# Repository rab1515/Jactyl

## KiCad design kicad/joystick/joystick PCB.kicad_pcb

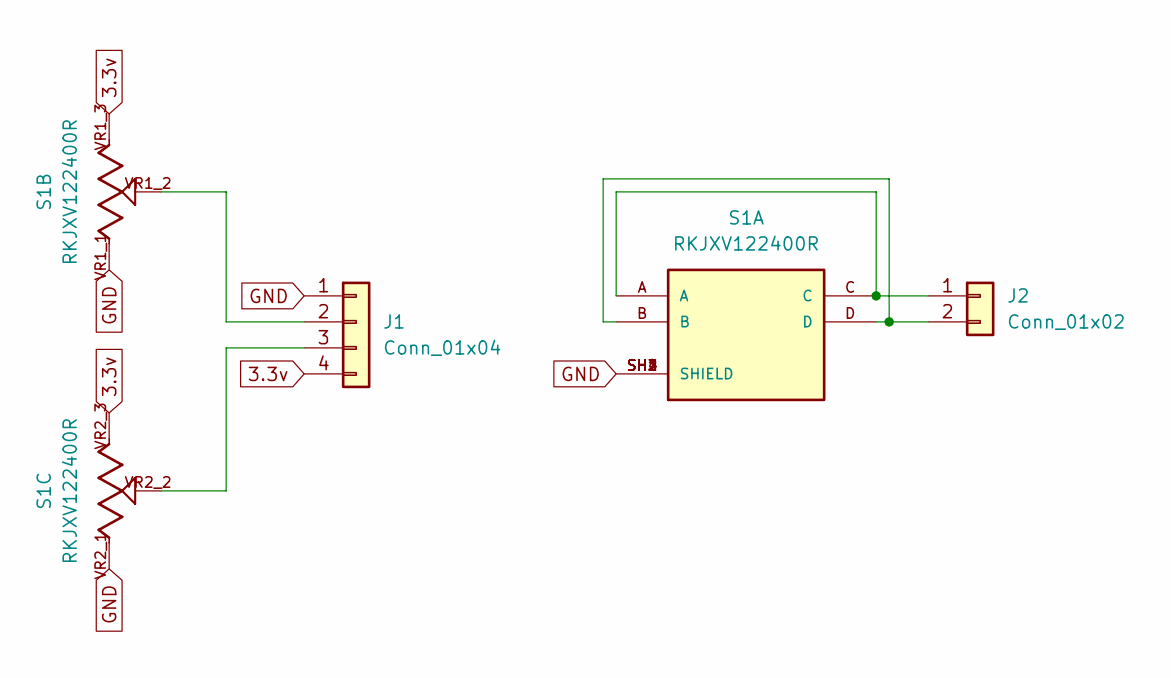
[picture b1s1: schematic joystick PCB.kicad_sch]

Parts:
J1: Conn_01x04; JST_PH_B4B-PH-K_1x04_P2.00mm_Vertical
J2: Conn_01x02; JST_PH_B2B-PH-K_1x02_P2.00mm_Vertical
S1: RKJXV122400R; SW_RKJXV122400R; PARTREV N/A

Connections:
3.3v: J1.4, S1.VR1_3, S1.VR2_3
GND: J1.1, S1.SH1 (SHIELD), S1.SH2 (SHIELD), S1.SH3 (SHIELD), S1.SH4 (SHIELD), S1.VR1_1, S1.VR2_1
unnamed: J1.2, S1.VR1_2
unnamed: J1.3, S1.VR2_2
unnamed: J2.1, S1.A, S1.C
unnamed: J2.2, S1.B, S1.D

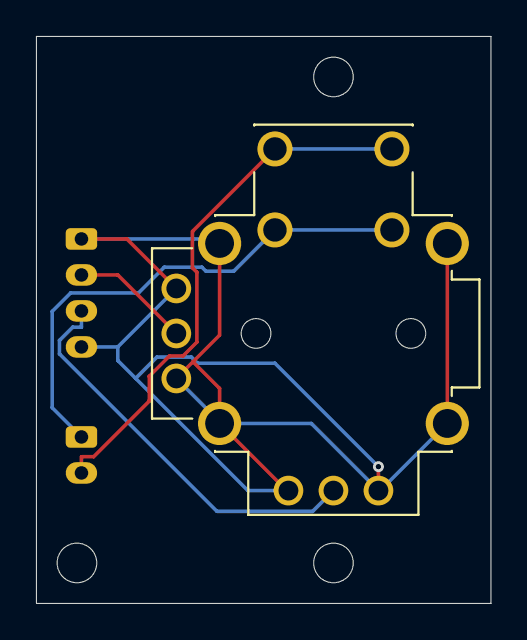
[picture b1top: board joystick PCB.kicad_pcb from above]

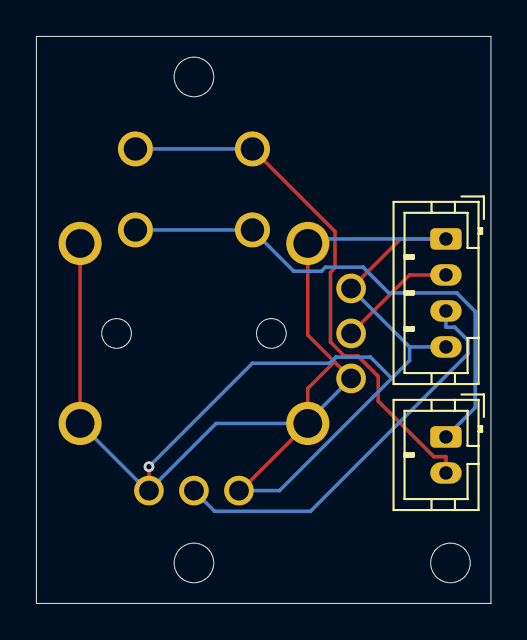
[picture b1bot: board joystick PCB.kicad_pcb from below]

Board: 2 copper layers, 25.2 x 31.5 mm, 6 parts (2 on the bottom side), 6 nets.

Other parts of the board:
void, void1, void2: MountingHole_2.2mm_M2_DIN965

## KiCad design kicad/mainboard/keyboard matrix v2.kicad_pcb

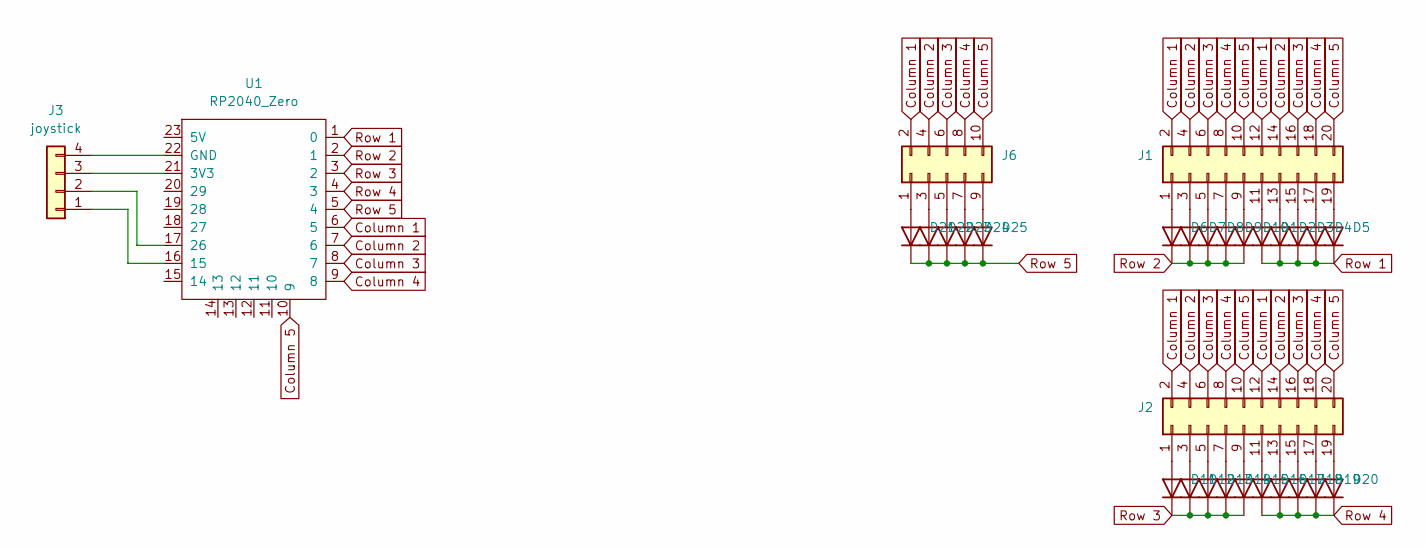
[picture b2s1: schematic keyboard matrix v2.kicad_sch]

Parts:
D1, D2, D3, D4, D5, D6, D7, D8, D9, D10, D11, D12, D13, D14, D15, D16, D17, D18, D19, D20, D21, D22, D23, D24, D25: Diode; Diode_DO-35
J1, J2: Conn_02x10_Odd_Even; PinHeader_2x10_P2.54mm_Vertical
J3: joystick; JST_PH_B4B-PH-K_1x04_P2.00mm_Vertical
J6: Conn_02x05_Odd_Even; PinHeader_2x05_P2.54mm_Vertical
U1: RP2040_Zero

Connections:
Column 1: J1.2, J1.12, J2.2, J2.12, J6.2, U1.6 (5)
Column 2: J1.4, J1.14, J2.4, J2.14, J6.4, U1.7 (6)
Column 3: J1.6, J1.16, J2.6, J2.16, J6.6, U1.8 (7)
Column 4: J1.8, J1.18, J2.8, J2.18, J6.8, U1.9 (8)
Column 5: J1.10, J1.20, J2.10, J2.20, J6.10, U1.10 (9)
unnamed: D1.2 (A), J1.11
unnamed: D2.2 (A), J1.13
unnamed: D3.2 (A), J1.15
unnamed: D4.2 (A), J1.17
unnamed: D5.2 (A), J1.19
unnamed: D6.2 (A), J1.1
unnamed: D7.2 (A), J1.3
unnamed: D8.2 (A), J1.5
unnamed: D9.2 (A), J1.7
unnamed: D10.2 (A), J1.9
unnamed: D11.2 (A), J2.1
unnamed: D12.2 (A), J2.3
unnamed: D13.2 (A), J2.5
unnamed: D14.2 (A), J2.7
unnamed: D15.2 (A), J2.9
unnamed: D16.2 (A), J2.11
unnamed: D17.2 (A), J2.13
unnamed: D18.2 (A), J2.15
unnamed: D19.2 (A), J2.17
unnamed: D20.2 (A), J2.19
unnamed: D21.2 (A), J6.1
unnamed: D22.2 (A), J6.3
unnamed: D23.2 (A), J6.5
unnamed: D24.2 (A), J6.7
unnamed: D25.2 (A), J6.9
unnamed: J3.1, U1.16 (15)
unnamed: J3.2, U1.17 (26)
unnamed: J3.3, U1.21 (3V3)
unnamed: J3.4, U1.22 (GND)
Row 1: D1.1 (K), D2.1 (K), D3.1 (K), D4.1 (K), D5.1 (K), U1.1 (0)
Row 2: D6.1 (K), D7.1 (K), D8.1 (K), D9.1 (K), D10.1 (K), U1.2 (1)
Row 3: D11.1 (K), D12.1 (K), D13.1 (K), D14.1 (K), D15.1 (K), U1.3 (2)
Row 4: D16.1 (K), D17.1 (K), D18.1 (K), D19.1 (K), D20.1 (K), U1.4 (3)
Row 5: D21.1 (K), D22.1 (K), D23.1 (K), D24.1 (K), D25.1 (K), U1.5 (4)

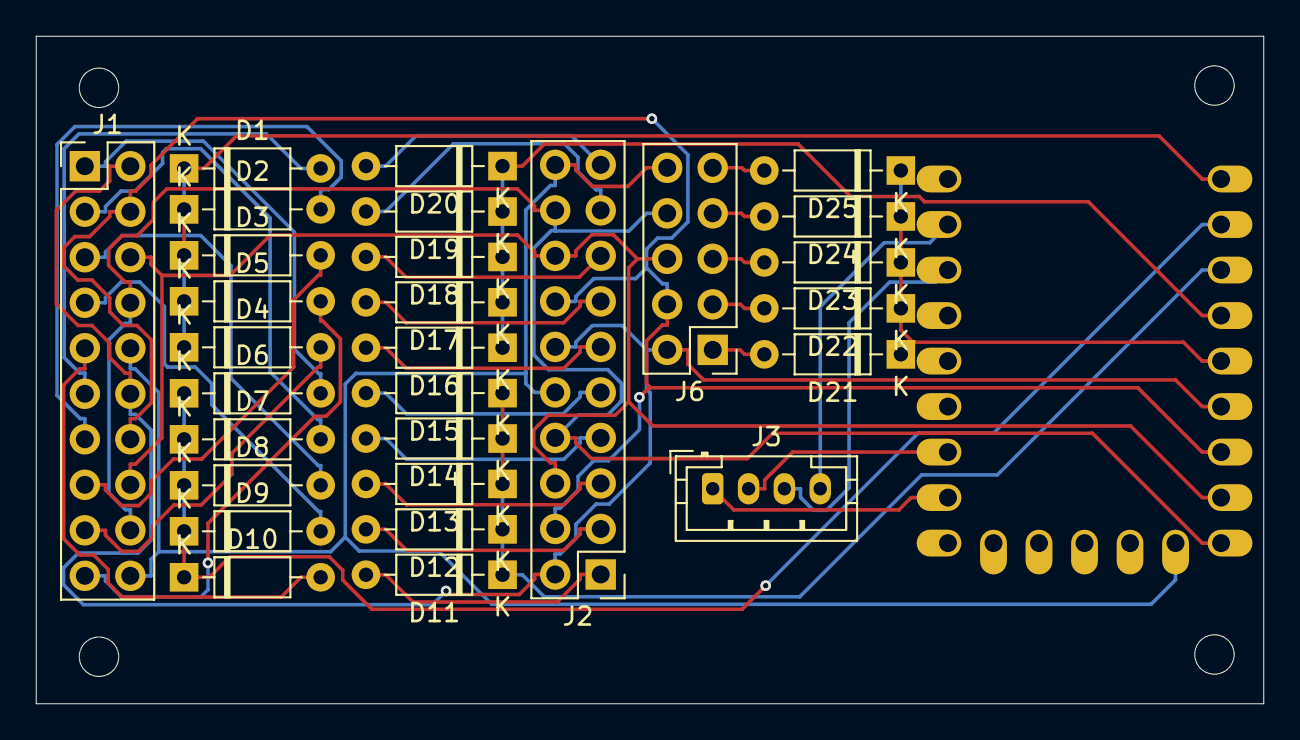
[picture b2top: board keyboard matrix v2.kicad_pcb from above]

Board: 2 copper layers, 68.5 x 37.2 mm, 34 parts (0 on the bottom side), 39 nets.

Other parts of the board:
foo, foo1, foo2, foo3: MountingHole_2.2mm_M2

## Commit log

2024-04-12 added kicad projects
2024-04-12 added photos and STL's
